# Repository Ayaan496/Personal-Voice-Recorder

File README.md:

A custom from scratch voice recorder.

(Prototype)Hardware: 
- Esp32 S3 Super mini
- I2S omnidirectional Microphone
- Button
- SSD1306 128x64 OLED display

How to Use:
- Currently on the prototype, it is only able to connect through serial. run the python script
  with the main c++ file uploaded to the esp-32 and it should start recording. Click again to
  end the recording and save the data to a recording.wav file.

Future Additions:
- While this is the prototype, the finished version will include an stl file for a
  3d printed casing as well as a kicad schematic for the custom PCB. the final project will have
  its own SD card as well as an option to transfer data through wifi.

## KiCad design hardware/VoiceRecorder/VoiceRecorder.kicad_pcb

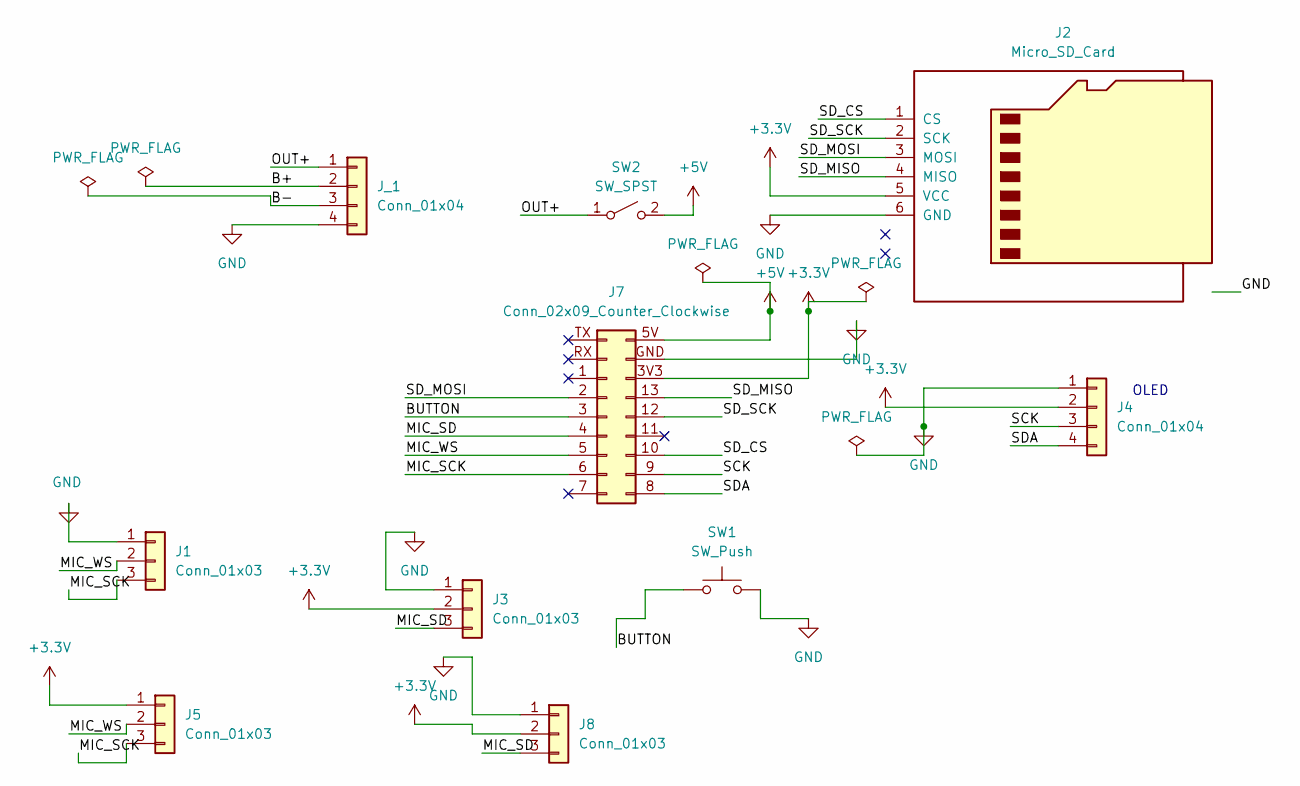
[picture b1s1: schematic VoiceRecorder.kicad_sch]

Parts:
J1, J3, J5, J8: Conn_01x03; PinHeader_1x03_P2.54mm_Vertical
J2: Micro_SD_Card; PinSocket_1x06_P2.54mm_Horizontal
J4: Conn_01x04; PinHeader_1x04_P2.54mm_Vertical
J7: Conn_02x09_Counter_Clockwise; ESP32-S3-SuperMini
J_1: Conn_01x04; PinHeader_1x04_P2.54mm_Vertical
SW1: SW_Push; SW_Tactile_Straight_KSA0Axx1LFTR
SW2: SW_SPST; PinHeader_1x02_P2.54mm_Vertical

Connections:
+3.3V: J2.5 (VCC), J3.2, J4.2, J5.1, J7.3V3 (Pin_16), J8.2
+5V: J7.5V (Pin_18), SW2.2 (B)
/B+: J_1.2
/B-: J_1.3
/BUTTON: J7.3 (Pin_5), SW1.1
/MIC_SCK: J1.3, J5.3, J7.6 (Pin_8)
/MIC_SD: J3.3, J7.4 (Pin_6), J8.3
/MIC_WS: J1.2, J5.2, J7.5 (Pin_7)
/OUT+: J_1.1, SW2.1 (A)
/SCK: J4.3, J7.9 (Pin_11)
/SDA: J4.4, J7.8 (Pin_10)
/SD_CS: J2.1 (CS), J7.10 (Pin_12)
/SD_MISO: J2.4 (MISO), J7.13 (Pin_15)
/SD_MOSI: J2.3 (MOSI), J7.2 (Pin_4)
/SD_SCK: J2.2 (SCK), J7.12 (Pin_14)
GND: J1.1, J2.6 (GND), J3.1, J4.1, J7.GND (Pin_17), J8.1, J_1.4, SW1.2

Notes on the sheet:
OLED

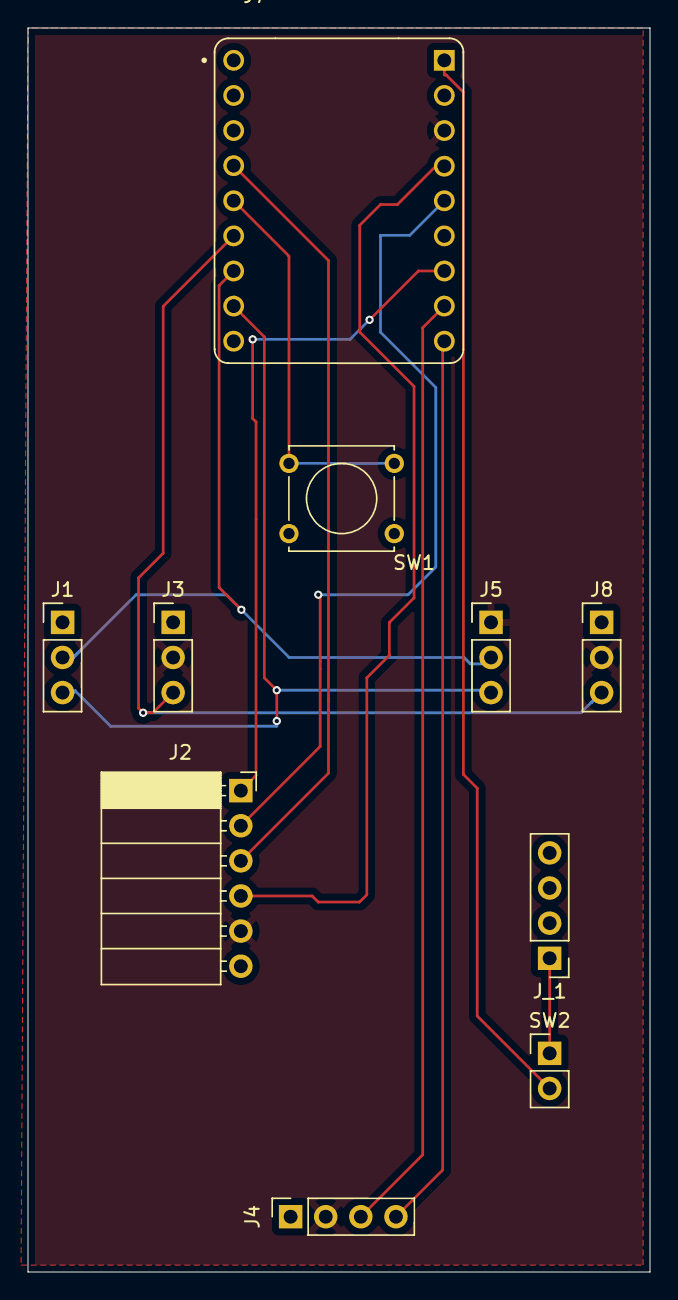
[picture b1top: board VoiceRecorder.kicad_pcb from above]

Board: 2 copper layers, 45.0 x 90.0 mm, 10 parts (0 on the bottom side), 14 nets.

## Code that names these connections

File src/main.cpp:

//Libraries
#include <Arduino.h>
#include <Wire.h>
#include <Adafruit_GFX.h>
#include <Adafruit_SSD1306.h>
#include <driver/i2s.h>
#include <SD.h>
#include <SPI.h>

//Pins
#define SDA_PIN 8
#define SCL_PIN 9
#define I2S_SD_PIN 4
#define I2S_WS_PIN 5
#define I2S_SCK_PIN 6
#define BUTTON_PIN 3

#define SD_CS_PIN 10
#define SD_SCK_PIN 12
#define SD_MOSI_PIN 2
#define SD_MISO_PIN 13

//I2S config
#define I2S_PORT I2S_NUM_0
#define SAMPLE_RATE 16000
#define BUFFER_SIZE 512


//Variables
bool lastButtonState = HIGH;
Adafruit_SSD1306 display(128,64,&Wire, -1);
bool isRecording = false;
int recordingSeconds = 0;
unsigned long lastSecondTick = 0;
int32_t audioBuffer[BUFFER_SIZE];
File audioFile;
int fileIndex = 0;




//I2S setup
void setupI2S(){
  //config struct
  i2s_config_t config = {
    .mode                 = (i2s_mode_t)(I2S_MODE_MASTER | I2S_MODE_RX),//Recieve only
    .sample_rate          = SAMPLE_RATE,
    .bits_per_sample      = I2S_BITS_PER_SAMPLE_32BIT,
    .channel_format       = I2S_CHANNEL_FMT_RIGHT_LEFT,//Stereo, switch to _ONLY_LEFT for mono
    .communication_format = I2S_COMM_FORMAT_STAND_I2S,
    .intr_alloc_flags     = ESP_INTR_FLAG_LEVEL1,
    .dma_buf_count        = 4,
    .dma_buf_len          = BUFFER_SIZE,
    .use_apll             = false,
    .tx_desc_auto_clear   = false,
    .fixed_mclk           = 0
  };

  i2s_pin_config_t pins = {

    .bck_io_num = I2S_SCK_PIN,
    .ws_io_num = I2S_WS_PIN,
    .data_out_num = I2S_PIN_NO_CHANGE, //No data out
    .data_in_num = I2S_SD_PIN

  };

  //I2s activation
  i2s_driver_install(I2S_PORT, &config, 0, NULL);
  i2s_set_pin(I2S_PORT, &pins);
  i2s_start(I2S_PORT);

}

// Write a 32 bit integer to file in little endian
void writeInt32(File &f, int32_t value) {
  f.write((uint8_t*)&value, 4);
}

void writeInt16(File &f, int16_t value) {
  f.write((uint8_t*)&value, 2);
}



void writeWavHeader(File &f, int sampleRate, int numChannels) {
  f.write((const uint8_t*)"RIFF", 4);
  writeInt32(f, 0);
  f.write((const uint8_t*)"WAVE", 4);
  f.write((const uint8_t*)"fmt ", 4);
  writeInt32(f, 16);
  writeInt16(f, 1);
  writeInt16(f, numChannels);
  writeInt32(f, sampleRate);
  writeInt32(f, sampleRate * numChannels * 2);
  writeInt16(f, numChannels * 2);
  writeInt16(f, 16);
  f.write((const uint8_t*)"data", 4);
  writeInt32(f, 0);
}



void finalizeWavHeader(File &f) {
  uint32_t fileSize = f.size();
  uint32_t dataSize = fileSize - 44;  // 44 bytes is the WAV header size

  f.seek(4);
  writeInt32(f, fileSize - 8);  // RIFF chunk size

  f.seek(40);
  writeInt32(f, dataSize);      // data chunk size
}

//display idle screen
void showIdle(){

  display.clearDisplay();
  display.setTextSize(1);
  display.setTextColor(SSD1306_WHITE);
  display.setCursor(0, 0);
  display.println("  Audio Recorder");
  display.drawLine(0, 12, 128, 12, SSD1306_WHITE);
  display.setCursor(0, 20);
  display.println("Tap button to");
  display.println("record audio.");
  display.setCursor(0, 50);
  display.println("Status: IDLE");
  display.display();
}

//display recording screen
void showRecording(int seconds) {
  display.clearDisplay();
  display.setTextSize(1);
  display.setTextColor(SSD1306_WHITE);
  display.setCursor(0, 0);
  display.println("  Audio Recorder");
  display.drawLine(0, 12, 128, 12, SSD1306_WHITE);

    // Flashing REC indicator
  if ((millis() / 500) % 2 == 0) { //fashing circle every half second
    display.fillCircle(6, 28, 5, SSD1306_WHITE);
  }
  display.setTextSize(2);
  display.setCursor(16, 20);
  display.println("REC");

  display.setTextSize(1);
  display.setCursor(0, 44);
  display.print("Time: ");
  display.print(seconds);
  display.println("s");

  display.setCursor(0, 54);
  display.println("Click again to stop");
  display.display();
}
//display saved screen
void showSaved(int seconds, String filename) {
  display.clearDisplay();
  display.setTextSize(1);
  display.setTextColor(SSD1306_WHITE);
  display.setCursor(0, 0);
  display.println("  Audio Recorder");
  display.drawLine(0, 12, 128, 12, SSD1306_WHITE);
  display.setTextSize(2);
  display.setCursor(20, 20);
  display.println("SAVED");
  display.setTextSize(1);
  display.setCursor(0, 44);
  display.print("Duration: ");
  display.print(seconds);
  display.println("s");
  display.setCursor(0, 54);
  display.println(filename);
  display.display();
}

void showError(String message) {
  display.clearDisplay();
  display.setTextSize(1);
  display.setTextColor(SSD1306_WHITE);
  display.setCursor(0, 0);
  display.println("  Audio Recorder");
  display.drawLine(0, 12, 128, 12, SSD1306_WHITE);
  display.setCursor(0, 20);
  display.println("ERROR:");
  display.println(message);
  display.display();
}

void setup() {
  Serial.begin(921600);
  pinMode(BUTTON_PIN, INPUT_PULLUP);
  Wire.begin(SDA_PIN, SCL_PIN);

  //start the display and check if its findable
  if (!display.begin(SSD1306_SWITCHCAPVCC, 0x3C)){
    
    Serial.println("Display not found");
    while(true);
  }

  // Start SPI for SD card
  SPI.begin(SD_SCK_PIN, SD_MISO_PIN, SD_MOSI_PIN, SD_CS_PIN);
  if (!SD.begin(SD_CS_PIN)) {
    showError("SD card not found");
    Serial.println("SD card not found");
    while (true);
  }
  Serial.println("SD card ready");




  setupI2S();
  delay(100);
  lastSecondTick = millis();
  showIdle();
 

}

//send audio data over serial
void sendAudioOverSerial(int32_t* buffer, size_t samples){
  Serial.write((uint8_t*)buffer, samples * sizeof(int32_t));
}

void loop() {

  //Button logic
  bool currentButtonState = digitalRead(BUTTON_PIN);

  if (currentButtonState == LOW && lastButtonState == HIGH) {
    lastButtonState = currentButtonState;
    delay(50); //debounce

    //if button is pressed and not recording, start recording and start counting time
    if (digitalRead(BUTTON_PIN) == LOW) {
      if (!isRecording) {


        // Create a new file with incrementing name e.g. REC001.wav
        String filename = "/REC";
        if (fileIndex < 10) filename += "00";
        else if (fileIndex < 100) filename += "0";
        filename += String(fileIndex) + ".wav";
        fileIndex++;

        audioFile = SD.open(filename, FILE_WRITE);
        if (!audioFile) {
          showError("Cannot open file");
          return;
        }

        writeWavHeader(audioFile, SAMPLE_RATE, 2);


        isRecording = true;
        recordingSeconds = 0;
        lastSecondTick = millis();
        
        Serial.write("START");//send to python script
        showRecording(0);
      } else { //if button pressed and you are recording, stop recording
        isRecording = false;

        finalizeWavHeader(audioFile);
        audioFile.close();

        Serial.println("Recording stopped");
        
        Serial.write("STOP");
        showSaved(recordingSeconds, "/REC" + String(fileIndex - 1) + ".wav");

        delay(2000);
        showIdle();
      }
    }
  }

  lastButtonState = currentButtonState;

  //take data from dma buffer and put it into audio buffer
  if (isRecording) {
    size_t bytesRead = 0;
    i2s_read(I2S_PORT, audioBuffer, sizeof(audioBuffer), &bytesRead, pdMS_TO_TICKS(10));
    //if data was read, send the data over serial
     if (bytesRead > 0) {
      sendAudioOverSerial(audioBuffer, bytesRead / sizeof(int32_t));
      // Convert 32 bit samples to 16 bit and write to SD card
      size_t numSamples = bytesRead / sizeof(int32_t);
      for (size_t i = 0; i < numSamples; i++) {
        int16_t sample = (int16_t)(max(-32768, min(32767, audioBuffer[i] >> 10)));
        audioFile.write((uint8_t*)&sample, 2);
      }

    // Only stream over serial if connected
    if (Serial) {
      sendAudioOverSerial(audioBuffer, bytesRead / sizeof(int32_t));
  }
    }


    //increment recording seconds every second
    if (millis() - lastSecondTick >= 1000) {
      recordingSeconds++;
      lastSecondTick = millis();
      showRecording(recordingSeconds);
    }
  }
}

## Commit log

2026-03-14 Voice Recorder Prototype
2026-03-14 changed from Mono to Stereo
2026-03-14 Added comments to main.cpp
2026-03-16 Added SD card capabilities as well as battery powered the prototype. Added Kicad schematic of PCB for the Voice Recorder
2026-03-19 finished pcb design
